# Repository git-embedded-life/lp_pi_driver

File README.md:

# Overview
Many years back we purchased two twin size Leggett & Platt adjustable bed foundations that were supposed to work in tandem to "adjust" a king size mattress. Unfortunately, they wre never consistent. 

The driver/controllers for each foundation used some RF comms between the two foundations and remotes that would move the two foundations in sync, and you wouldn't have half the mattress in a different configuration than the other half. The process to get the two foundation in synch was a bit cumbersome, having to press buttons in certain sequences on one while holding buttons on the other. Once they were in synch it worked great, until it didn't.

We were finding that after a short period of time the driver/controllers would lose sync with the other so when we would use the RF remote to adjust the bed, only half the bed would adjust. I would go through the process of synching the two again and shortly after they would lose their mind once again. We tried installing a new driver/controller, swapping driver/controllers, nothing would provide an experience that would last. Eventually I gave up and said, I could make something that would work consistently. Welcome to this project.

# Details
When going into this project my gaols were a system that I could control via Wifi, and that matches the connectors on the existing hardware so I did not have to cut cables. For the controller portion I landed on a Pi Zero W (this was before there was a shortage). The Pi would serve up a web page in Python that would then send signals to two drivers, one attached to each bed foundation. The drivers would be dumb devices that simply took discrete inputs and would turn replays on and off. The drivers also had to be responsible for stopping when limit switches were tripped.

## Bed Driver
<image src="images/driver_board.jpg" width="40%">&nbsp;&nbsp;&nbsp;&nbsp;
<image src="images/board_box.jpg" width="40%">

The driver takes discrete inputs via a RJ45 input, that feed into a couple logic devices to prevent potentially damaging configurations, and control 4 relays. Overall I tried to keep this board as basic a possible.

## PI RJ45 Interface
The purpose of this board is two provide a connection between the RJ45 cables carrying the discrete signals and the PI's GPIO.

## UI
<image src="images/ui.jpg" width="30%">

I want to start this one with, I am NOT a good UI designer. I shoot for functionality and typically stop there. The UI is served up by bottle. The Python back end takes the inputs from the UI and drives the Pi's GPIO's. It also has a state machine to determine when a limit has been tripped based on feedback from the motor.

# Installation

```
systemctl link /home/pi/lp_pi_driver/bed_ctl.service

systemctl enable bed_ctl.service

systemctl start bed_ctl.service
```

# Materials
## Driver Board
- [OshPark Link to order](https://oshpark.com/shared_projects/JDcTUy17)

## Pi RJ45 Board
- [OshPark Link to order](https://oshpark.com/shared_projects/Bbv4X0oO)

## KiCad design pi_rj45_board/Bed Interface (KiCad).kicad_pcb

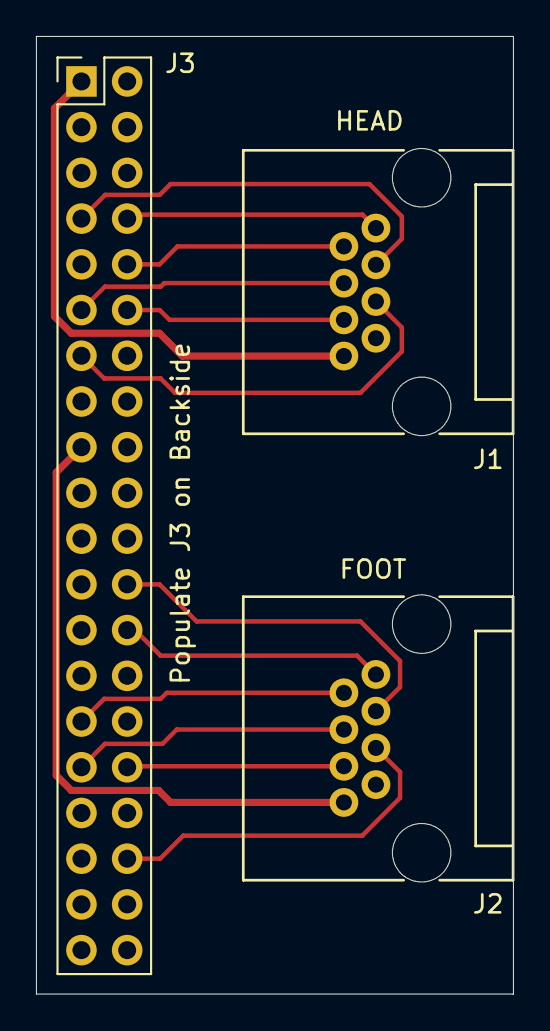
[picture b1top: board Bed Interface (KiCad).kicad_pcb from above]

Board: 2 copper layers, 26.5 x 53.2 mm, 3 parts (0 on the bottom side), 15 nets.

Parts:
J1, J2: RJ45; RJ45_Amphenol_RJHSE5080
J3: Conn_02x20_Odd_Even; PinHeader_2x20_P2.54mm_Vertical

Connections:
/FOOT_DOWN_A: J1.6, J3.12
/FOOT_DOWN_B: J2.6, J3.32
/FOOT_POSITION_A: J1.2, J3.10
/FOOT_POSITION_B: J2.2, J3.29
/FOOT_UP_A: J1.3, J3.7
/FOOT_UP_B: J2.3, J3.24
/HEAD_DOWN_A: J1.5, J3.13
/HEAD_DOWN_B: J2.5, J3.36
/HEAD_POSITION_A: J1.1, J3.8
/HEAD_POSITION_B: J2.1, J3.26
/HEAD_UP_A: J1.4, J3.11
/HEAD_UP_B: J2.4, J3.31
GND: J1.7, J2.7, J3.6, J3.9, J3.14, J3.20, J3.25, J3.30, J3.34, J3.39
unnamed: J1.8, J3.1
unnamed: J2.8, J3.17

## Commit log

2022-04-09 pushing up python web interface
2022-04-09 added some dteail to the readme
2022-04-09 pushed up rj45 board and added oshpark links
